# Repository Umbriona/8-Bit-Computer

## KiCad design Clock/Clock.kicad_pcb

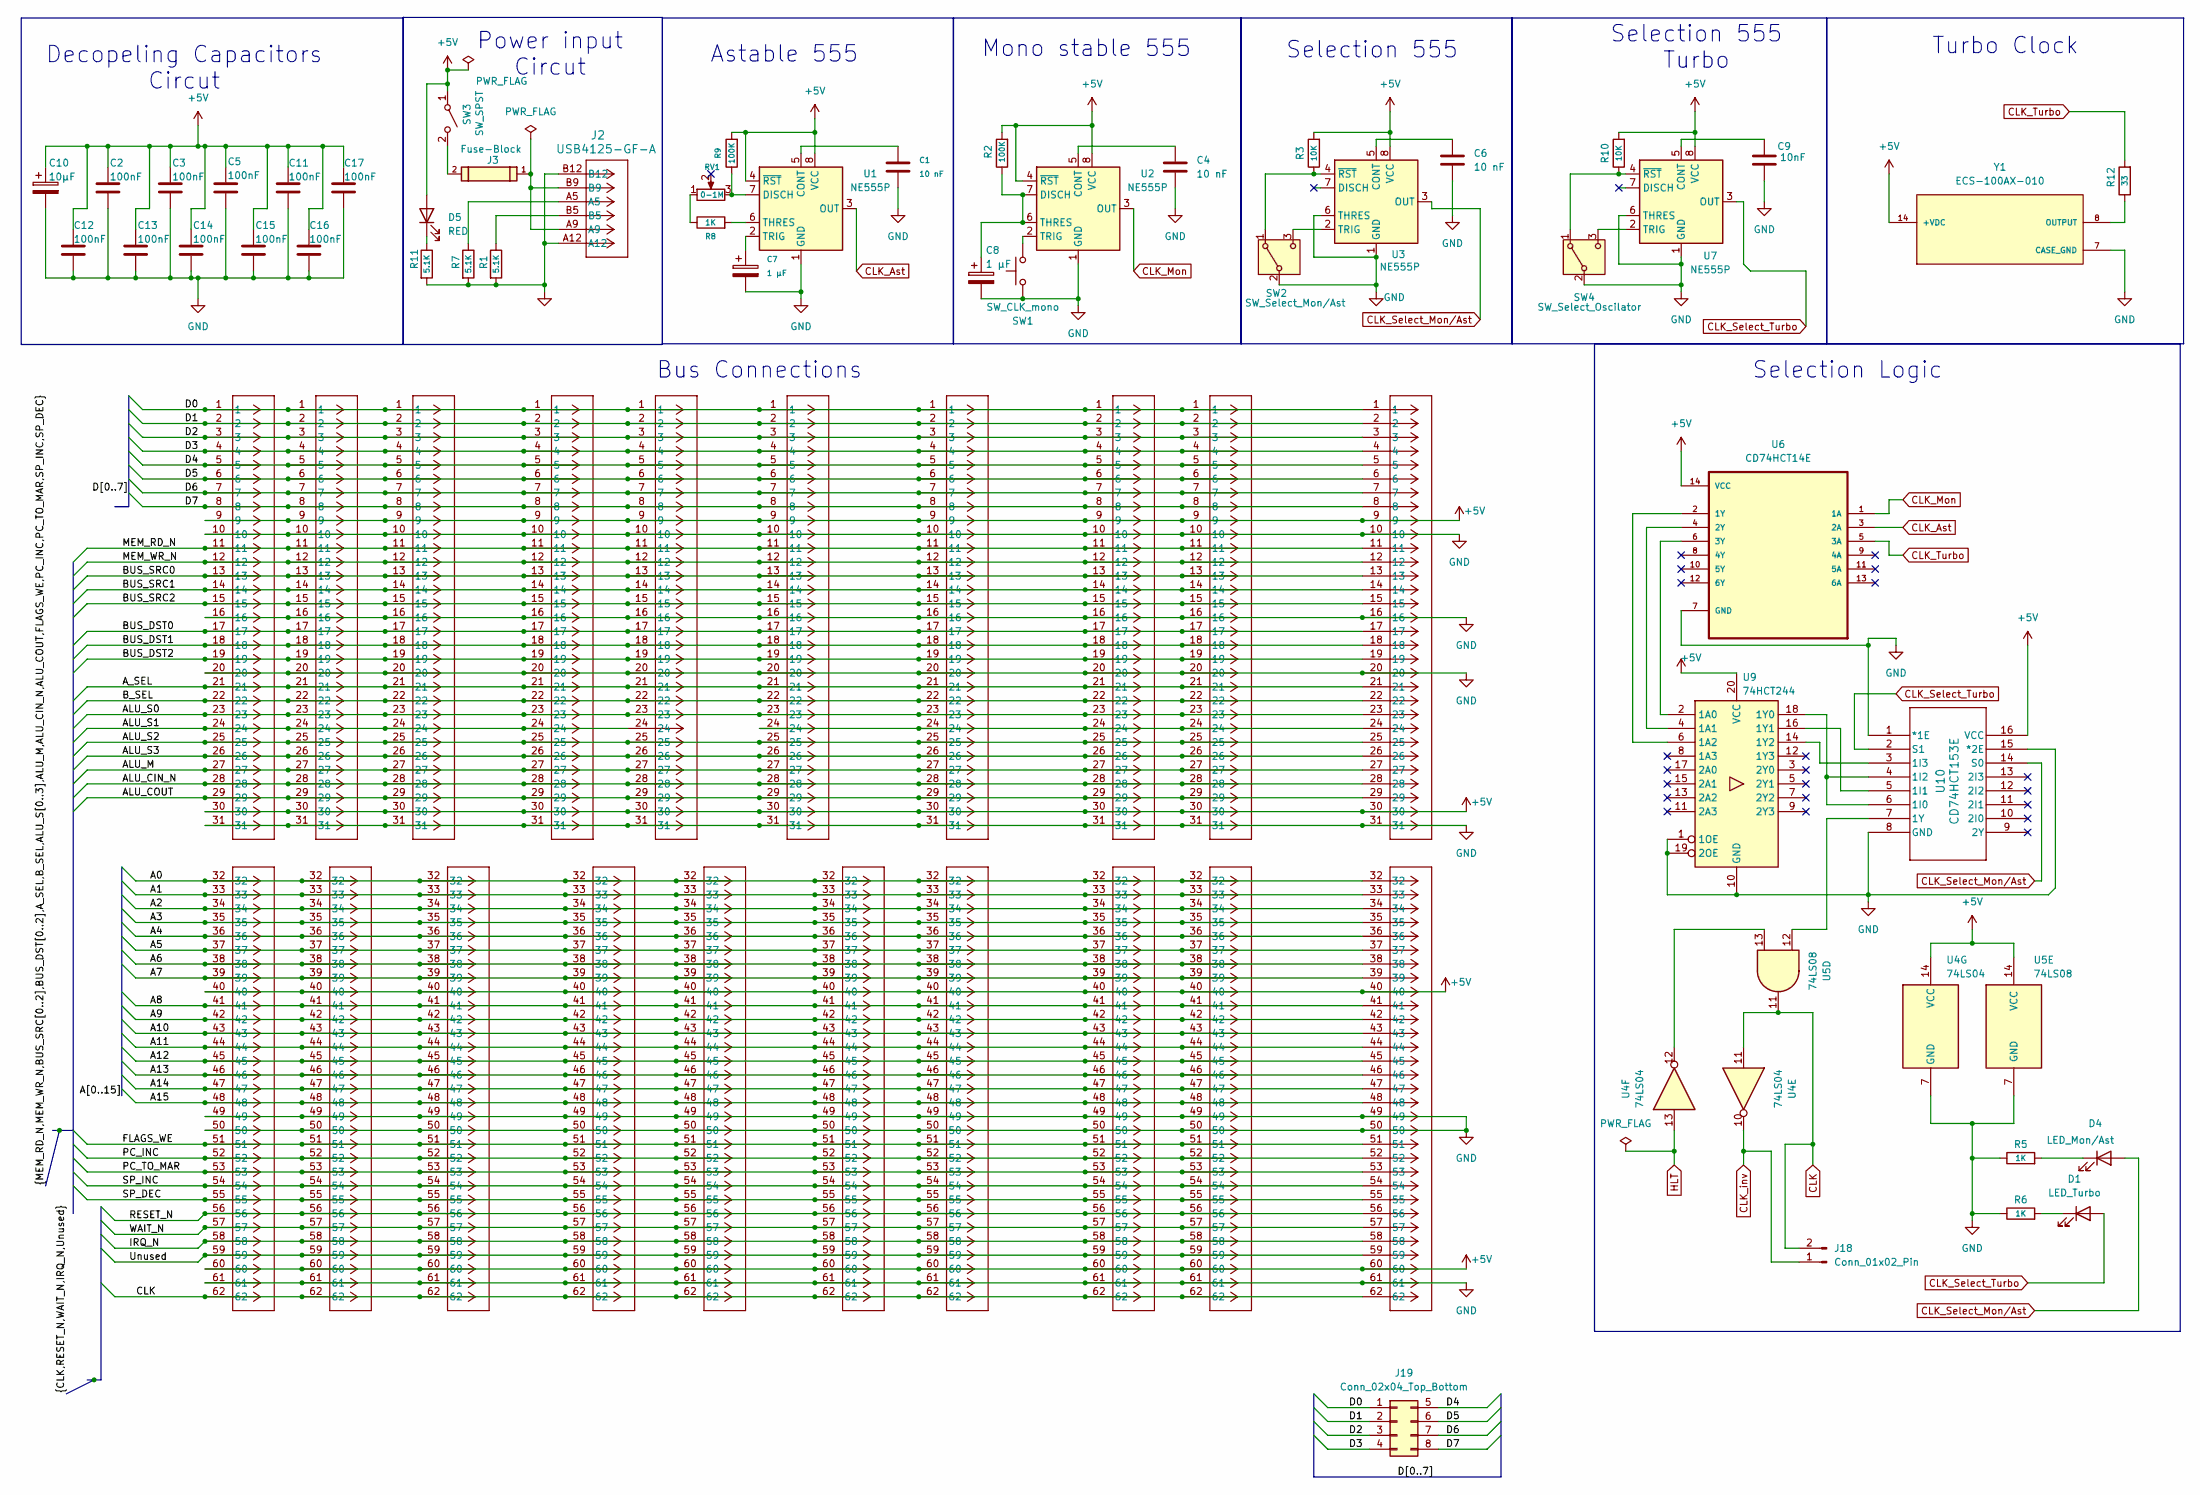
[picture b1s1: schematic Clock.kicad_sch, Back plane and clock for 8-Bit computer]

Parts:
C1, C4, C6: 10 nF; C_Disc_D3.0mm_W2.0mm_P2.50mm
C2, C3, C5, C11, C12, C13, C14, C15, C16, C17: 100nF; C_Disc_D3.0mm_W2.0mm_P2.50mm
C7, C8: 1 μF; CP_Radial_D4.0mm_P2.00mm
C9: 10nF; C_Disc_D3.0mm_W2.0mm_P2.50mm
C10: 10μF; CP_Radial_D5.0mm_P2.00mm
D1: LED_Turbo; LED_D5.0mm
D4: LED_Mon/Ast; LED_D5.0mm
D5: RED; LED_D5.0mm
J1, J4: Conn buss; CONN_520-350_EDA
J2: USB4125-GF-A; CONN6_USB4125_GCT
J3: Fuse-Block; 696108003002
J5, J6, J7, J8, J9, J10, J11, J12: Conn_buss; CONN_520-350_EDA
J18: Conn_01x02_Pin; PinHeader_1x02_P2.54mm_Vertical
J19: Conn_02x04_Top_Bottom; PinHeader_2x04_P2.54mm_Vertical
R1, R7, R11: 5.1K; R_Axial_DIN0204_L3.6mm_D1.6mm_P5.08mm_Horizontal
R2, R9: 100K; R_Axial_DIN0204_L3.6mm_D1.6mm_P5.08mm_Horizontal
R3, R10: 10K; R_Axial_DIN0204_L3.6mm_D1.6mm_P5.08mm_Horizontal
R5, R6, R8: 1K; R_Axial_DIN0204_L3.6mm_D1.6mm_P5.08mm_Horizontal
R12: 33; R_Axial_DIN0204_L3.6mm_D1.6mm_P5.08mm_Horizontal
RV1: 0-1M; PinHeader_1x03_P2.54mm_Vertical
SW1: SW_CLK_mono; PinHeader_1x02_P2.54mm_Vertical
SW2: SW_Select_Mon/Ast; PinHeader_1x03_P2.54mm_Vertical
SW3: SW_SPST; PinHeader_1x02_P2.54mm_Vertical
SW4: SW_Select_Oscilator; PinHeader_1x03_P2.54mm_Vertical
U1, U2, U3, U7: NE555P; DIP-8_W7.62mm
U4: 74LS04; DIP-14_W7.62mm
U5: 74LS08; DIP-14_W7.62mm
U6: CD74HCT14E
U9: 74HCT244
U10: CD74HCT153E; 74HCT153
Y1: ECS-100AX-010; OSC_ECS-100AX-010

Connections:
+5V: C2.1, C3.1, C5.1, C10.1, C11.1, C12.1, C13.1, C14.1, C15.1, C16.1, C17.1, D5.2 (A), J1.9, J1.30, J1.40, J1.60, J4.9, J4.30, J4.40, J4.60, J5.9, J5.30, J5.40, J5.60, J6.9, J6.30, J6.40, J6.60, J7.9, J7.30, J7.40, J7.60, J8.9, J8.30, J8.40, J8.60, J9.9, J9.30, J9.40, J9.60, J10.9, J10.30, J10.40, J10.60, J11.9, J11.30, J11.40, J11.60, J12.9, J12.30, J12.40, J12.60, R2.2, R3.2, R9.2, R10.2, SW3.1 (A), U1.4 (~RST), U1.8 (VCC), U2.4 (~RST), U2.8 (VCC), U3.8 (VCC), U4.14 (VCC), U5.14 (VCC), U6.14 (VCC), U7.8 (VCC), U9.20 (VCC), U10.16 (VCC), Y1.14 (+VDC)
/A0: J1.32, J4.32, J5.32, J6.32, J7.32, J8.32, J9.32, J10.32, J11.32, J12.32
/A1: J1.33, J4.33, J5.33, J6.33, J7.33, J8.33, J9.33, J10.33, J11.33, J12.33
/A2: J1.34, J4.34, J5.34, J6.34, J7.34, J8.34, J9.34, J10.34, J11.34, J12.34
/A3: J1.35, J4.35, J5.35, J6.35, J7.35, J8.35, J9.35, J10.35, J11.35, J12.35
/A4: J1.36, J4.36, J5.36, J6.36, J7.36, J8.36, J9.36, J10.36, J11.36, J12.36
/A5: J1.37, J4.37, J5.37, J6.37, J7.37, J8.37, J9.37, J10.37, J11.37, J12.37
/A6: J1.38, J4.38, J5.38, J6.38, J7.38, J8.38, J9.38, J10.38, J11.38, J12.38
/A7: J1.39, J4.39, J5.39, J6.39, J7.39, J8.39, J9.39, J10.39, J11.39, J12.39
/A8: J1.41, J4.41, J5.41, J6.41, J7.41, J8.41, J9.41, J10.41, J11.41, J12.41
/A9: J1.42, J4.42, J5.42, J6.42, J7.42, J8.42, J9.42, J10.42, J11.42, J12.42
/A10: J1.43, J4.43, J5.43, J6.43, J7.43, J8.43, J9.43, J10.43, J11.43, J12.43
/A11: J1.44, J4.44, J5.44, J6.44, J7.44, J8.44, J9.44, J10.44, J11.44, J12.44
/A12: J1.45, J4.45, J5.45, J6.45, J7.45, J8.45, J9.45, J10.45, J11.45, J12.45
/A13: J1.46, J4.46, J5.46, J6.46, J7.46, J8.46, J9.46, J10.46, J11.46, J12.46
/A14: J1.47, J4.47, J5.47, J6.47, J7.47, J8.47, J9.47, J10.47, J11.47, J12.47
/A15: J1.48, J4.48, J5.48, J6.48, J7.48, J8.48, J9.48, J10.48, J11.48, J12.48
/ALU_CIN_N: J1.28, J4.28, J5.28, J6.28, J7.28, J8.28, J9.28, J10.28, J11.28, J12.28
/ALU_COUT: J1.29, J4.29, J5.29, J6.29, J7.29, J8.29, J9.29, J10.29, J11.29, J12.29
/ALU_M: J1.27, J4.27, J5.27, J6.27, J7.27, J8.27, J9.27, J10.27, J11.27, J12.27
/ALU_S0: J1.23, J4.23, J5.23, J6.23, J7.23, J8.23, J9.23, J10.23, J11.23, J12.23
/ALU_S2: J1.25, J4.25, J5.25, J6.25, J7.25, J8.25, J9.25, J10.25, J11.25, J12.25
/ALU_S3: J1.26, J4.26, J5.26, J6.26, J7.26, J8.26, J9.26, J10.26, J11.26, J12.26
/A_SEL: J1.21, J4.21, J5.21, J6.21, J7.21, J8.21, J9.21, J10.21, J11.21, J12.21
/BUS_DST0: J1.17, J4.17, J5.17, J6.17, J7.17, J8.17, J9.17, J10.17, J11.17, J12.17
/BUS_DST1: J1.18, J4.18, J5.18, J6.18, J7.18, J8.18, J9.18, J10.18, J11.18, J12.18
/BUS_DST2: J1.19, J4.19, J5.19, J6.19, J7.19, J8.19, J9.19, J10.19, J11.19, J12.19
/BUS_SRC0: J1.13, J4.13, J5.13, J6.13, J7.13, J8.13, J9.13, J10.13, J11.13, J12.13
/BUS_SRC1: J1.14, J4.14, J5.14, J6.14, J7.14, J8.14, J9.14, J10.14, J11.14, J12.14
/BUS_SRC2: J1.15, J4.15, J5.15, J6.15, J7.15, J8.15, J9.15, J10.15, J11.15, J12.15
/B_SEL: J1.22, J4.22, J5.22, J6.22, J7.22, J8.22, J9.22, J10.22, J11.22, J12.22
/D0: J1.1, J4.1, J5.1, J6.1, J7.1, J8.1, J9.1, J10.1, J11.1, J12.1, J19.1
/D1: J1.2, J4.2, J5.2, J6.2, J7.2, J8.2, J9.2, J10.2, J11.2, J12.2, J19.2
/D2: J1.3, J4.3, J5.3, J6.3, J7.3, J8.3, J9.3, J10.3, J11.3, J12.3, J19.3
/D3: J1.4, J4.4, J5.4, J6.4, J7.4, J8.4, J9.4, J10.4, J11.4, J12.4, J19.4
/D4: J1.5, J4.5, J5.5, J6.5, J7.5, J8.5, J9.5, J10.5, J11.5, J12.5, J19.5
/D5: J1.6, J4.6, J5.6, J6.6, J7.6, J8.6, J9.6, J10.6, J11.6, J12.6, J19.6
/D6: J1.7, J4.7, J5.7, J6.7, J7.7, J8.7, J9.7, J10.7, J11.7, J12.7, J19.7
/D7: J1.8, J4.8, J5.8, J6.8, J7.8, J8.8, J9.8, J10.8, J11.8, J12.8, J19.8
/FLAGS_WE: J1.51, J4.51, J5.51, J6.51, J7.51, J8.51, J9.51, J10.51, J11.51, J12.51
/IRQ_N: J1.58, J4.58, J5.58, J6.58, J7.58, J8.58, J9.58, J10.58, J11.58, J12.58
/MEM_RD_N: J1.11, J4.11, J5.11, J6.11, J7.11, J8.11, J9.11, J10.11, J11.11, J12.11
/MEM_WR_N: J1.12, J4.12, J5.12, J6.12, J7.12, J8.12, J9.12, J10.12, J11.12, J12.12
/PC_INC: J1.52, J4.52, J5.52, J6.52, J7.52, J8.52, J9.52, J10.52, J11.52, J12.52
/PC_TO_MAR: J1.53, J4.53, J5.53, J6.53, J7.53, J8.53, J9.53, J10.53, J11.53, J12.53
/RESET_N: J1.56, J4.56, J5.56, J6.56, J7.56, J8.56, J9.56, J10.56, J11.56, J12.56
/SP_DEC: J1.55, J4.55, J5.55, J6.55, J7.55, J8.55, J9.55, J10.55, J11.55, J12.55
/SP_INC: J1.54, J4.54, J5.54, J6.54, J7.54, J8.54, J9.54, J10.54, J11.54, J12.54
/Unused: J1.59, J4.59, J5.59, J6.59, J7.59, J8.59, J9.59, J10.59, J11.59, J12.59
/WAIT_N: J1.57, J4.57, J5.57, J6.57, J7.57, J8.57, J9.57, J10.57, J11.57, J12.57
CLK: J1.62, J4.62, J5.62, J6.62, J7.62, J8.62, J9.62, J10.62, J11.62, J12.62, J18.2, U4.11, U5.11
CLK_Ast: U1.3 (OUT), U6.3 (2A)
CLK_Mon: U2.3 (OUT), U6.1 (1A)
CLK_Select_Mon/Ast: D4.2 (A), U3.3 (OUT), U10.14 (S0)
CLK_Select_Turbo: D1.2 (A), U7.3 (OUT), U10.2 (S1)
CLK_Turbo: R12.2, U6.5 (3A)
CLK_inv: J18.1, U4.10
GND: C1.2, C2.2, C3.2, C4.2, C5.2, C6.2, C7.2, C8.2, C9.2, C10.2, C11.2, C12.2, C13.2, C14.2, C15.2, C16.2, C17.2, J1.10, J1.16, J1.20, J1.31, J1.49, J1.50, J1.61, J2.A12, J2.B12, J4.10, J4.16, J4.20, J4.31, J4.49, J4.50, J4.61, J5.10, J5.16, J5.20, J5.31, J5.49, J5.50, J5.61, J6.10, J6.16, J6.20, J6.31, J6.49, J6.50, J6.61, J7.10, J7.16, J7.20, J7.31, J7.49, J7.50, J7.61, J8.10, J8.16, J8.20, J8.31, J8.49, J8.50, J8.61, J9.10, J9.16, J9.20, J9.31, J9.49, J9.50, J9.61, J10.10, J10.16, J10.20, J10.31, J10.49, J10.50, J10.61, J11.10, J11.16, J11.20, J11.31, J11.49, J11.50, J11.61, J12.10, J12.16, J12.20, J12.31, J12.49, J12.50, J12.61, R1.2, R5.1, R6.1, R7.2, R11.2, SW1.1, SW2.2 (B), SW4.2 (B), U1.1 (GND), U2.1 (GND), U3.1 (GND), U3.6 (THRES), U4.7 (GND), U5.7 (GND), U6.7 (GND), U7.1 (GND), U7.6 (THRES), U9.1 (1OE), U9.10 (GND), U9.19 (2OE), U10.1 (*1E), U10.8 (GND), U10.15 (*2E), Y1.7 (CASE_GND)
HLT: U4.13
unnamed: D1.1 (K), R6.2
unnamed: D4.1 (K), R5.2
unnamed: D5.1 (K), R11.1
unnamed: J2.A5, R7.1
unnamed: J2.A9, J2.B9, J3.1
unnamed: J2.B5, R1.1
unnamed: R8.1, RV1.1
unnamed: R3.1, SW2.1 (A), U3.4 (~RST)
unnamed: SW2.3 (C), U3.2 (TRIG)
unnamed: J3.2, SW3.2 (B)
unnamed: R10.1, SW4.1 (A), U7.4 (~RST)
unnamed: SW4.3 (C), U7.2 (TRIG)
unnamed: C1.1, U1.5 (CONT)
unnamed: R9.1, RV1.3, U1.7 (DISCH)
unnamed: R8.2, U1.6 (THRES)
unnamed: C7.1, U1.2 (TRIG)
unnamed: C4.1, U2.5 (CONT)
unnamed: C8.1, R2.1, U2.6 (THRES), U2.7 (DISCH)
unnamed: SW1.2, U2.2 (TRIG)
unnamed: C6.1, U3.5 (CONT)
unnamed: U4.12, U5.13
unnamed: U6.2 (1Y), U9.6 (1A2)
unnamed: U6.4 (2Y), U9.4 (1A1)
unnamed: U6.6 (3Y), U9.2 (1A0)
unnamed: C9.1, U7.5 (CONT)
unnamed: U9.18 (1Y0), U10.4 (1I2), U10.6 (1I0)
unnamed: U9.16 (1Y1), U10.5 (1I1)
unnamed: U9.14 (1Y2), U10.3 (1I3)
unnamed: U5.12, U10.7 (1Y)
unnamed: R12.1, Y1.8 (OUTPUT)

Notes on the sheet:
Selection 555
Astable 555
Mono stable 555
Power input Circut
Turbo Clock
Bus Connections
Selection 555 Turbo
Selection Logic
Decopeling Capacitors Circut

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
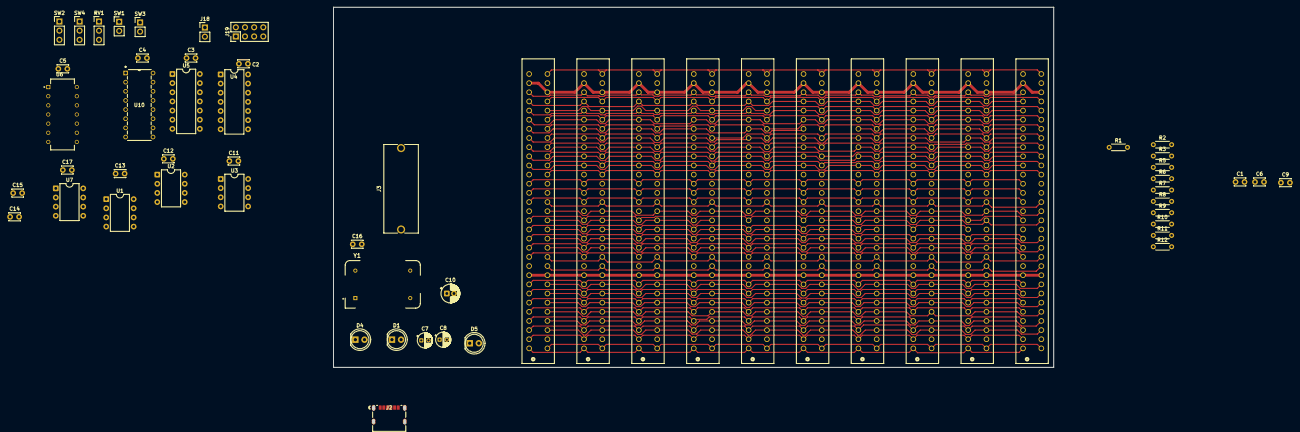
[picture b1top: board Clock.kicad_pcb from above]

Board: 2 copper layers, 200.0 x 115.4 mm, 59 parts (0 on the bottom side), 84 nets.

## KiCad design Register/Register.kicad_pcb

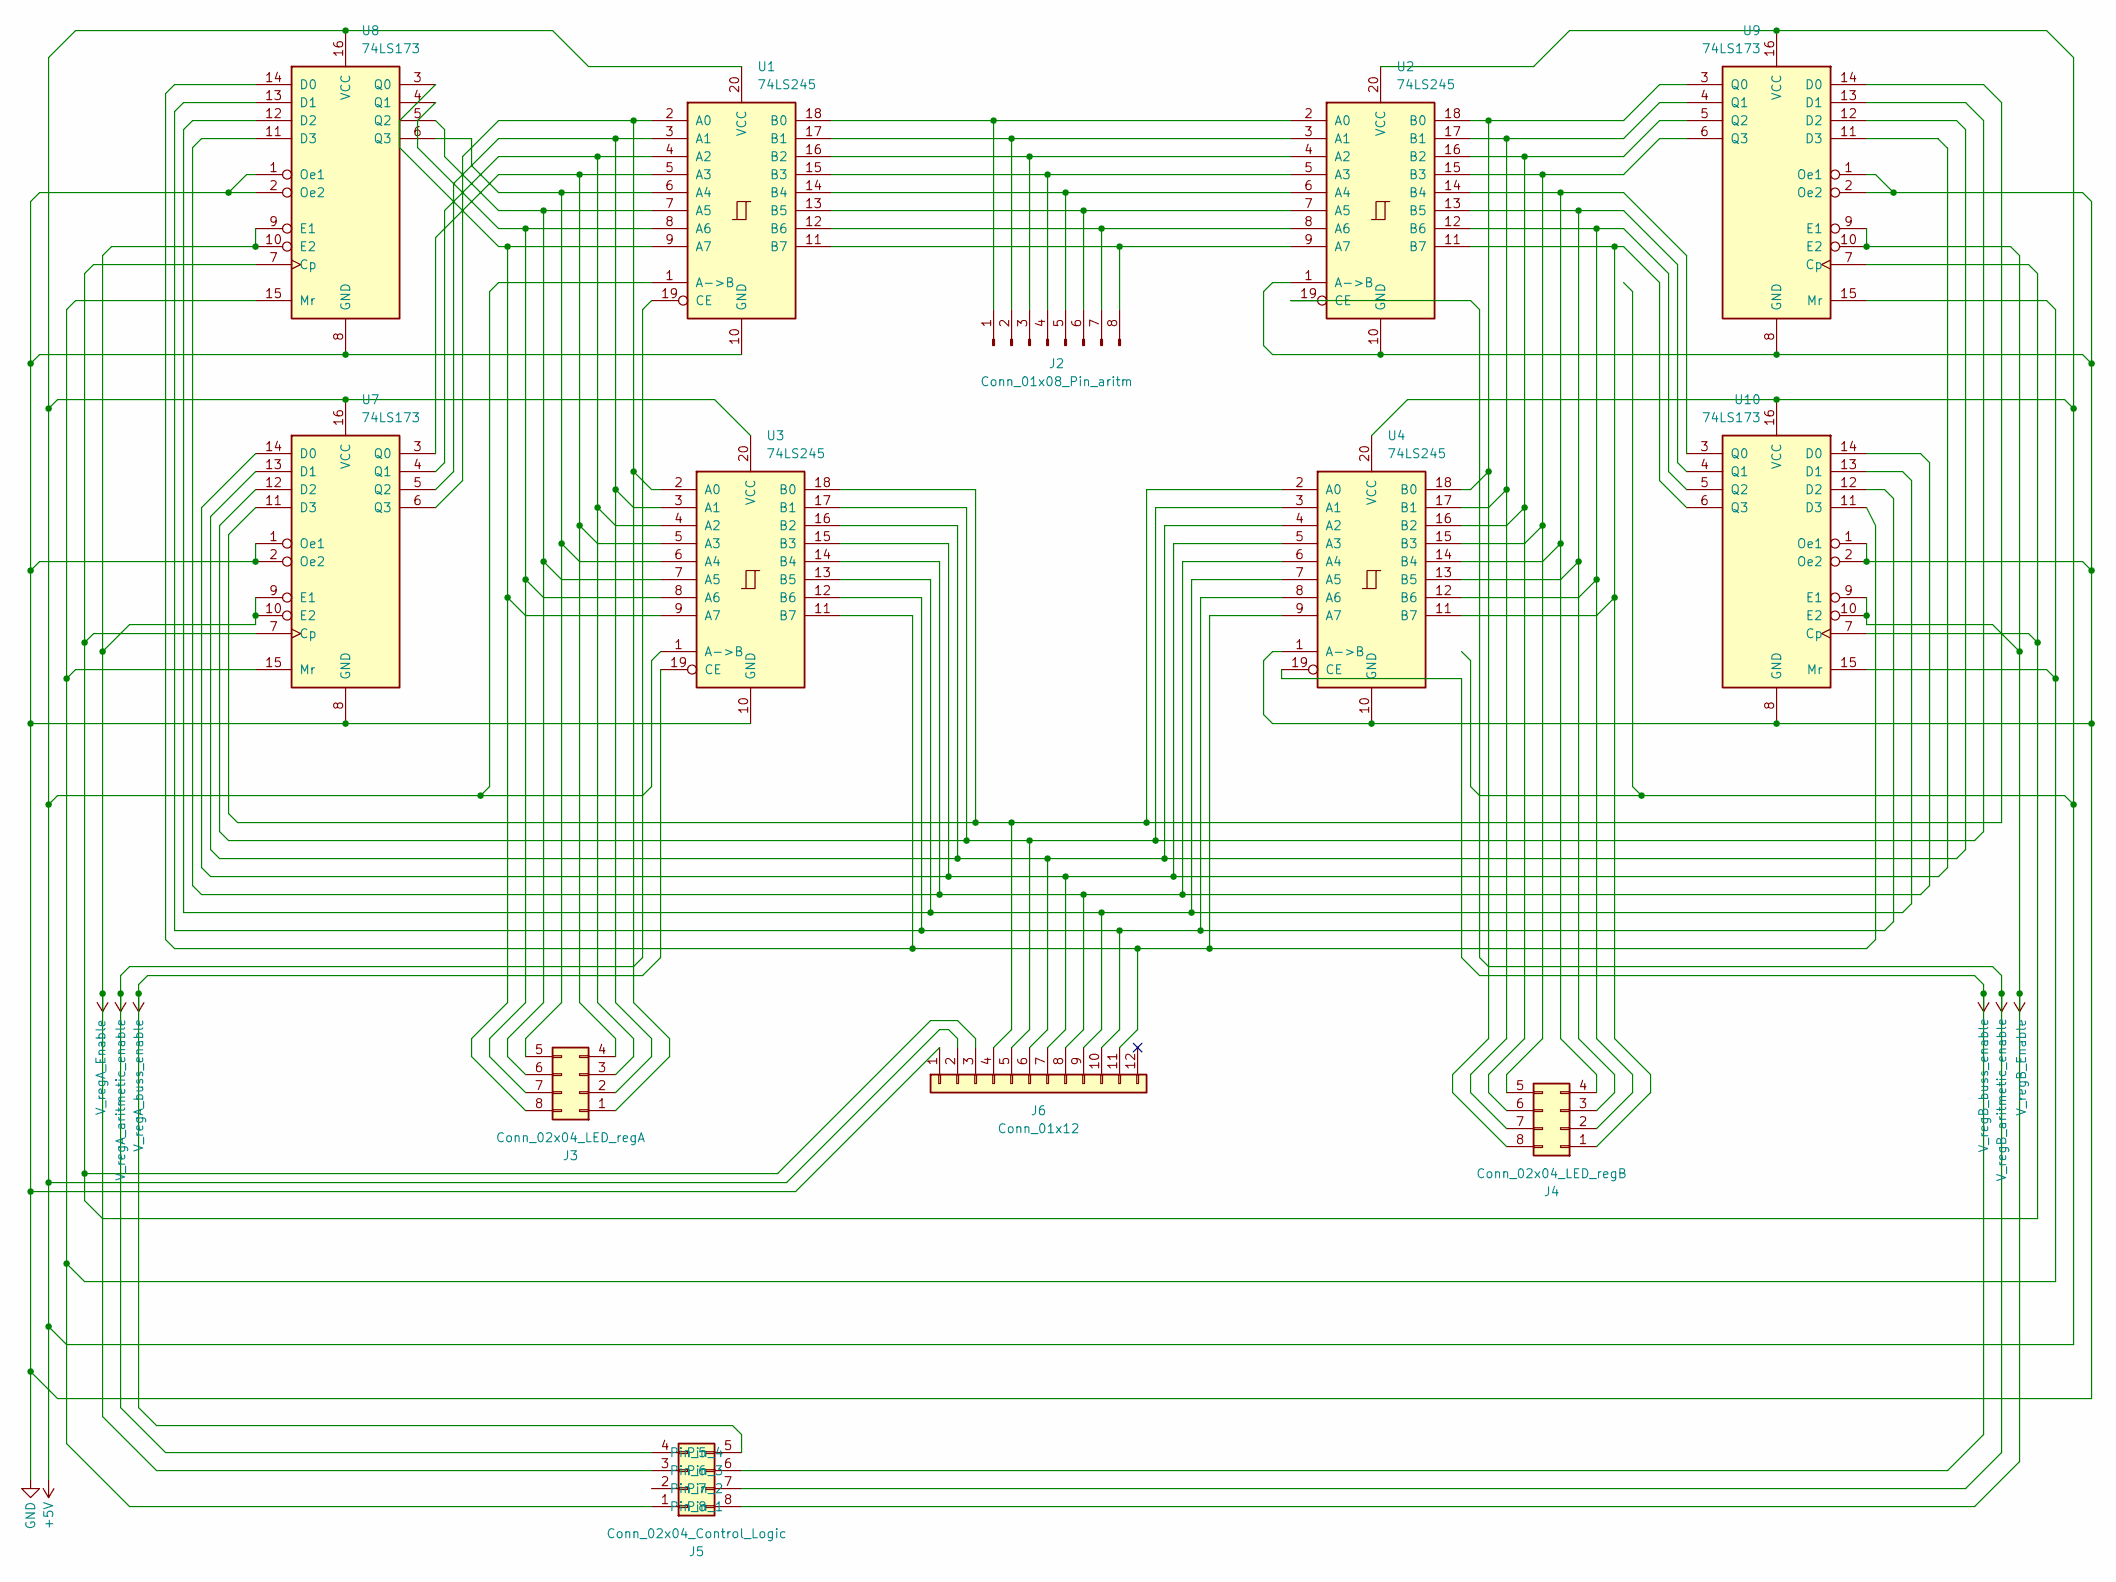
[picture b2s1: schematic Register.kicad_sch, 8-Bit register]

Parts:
J2: Conn_01x08_Pin_aritm; PinHeader_1x08_P2.54mm_Horizontal
J3: Conn_02x04_LED_regA; PinSocket_2x04_P2.54mm_Horizontal
J4: Conn_02x04_LED_regB; PinSocket_2x04_P2.54mm_Horizontal
J5: Conn_02x04_Control_Logic; PinSocket_2x04_P2.54mm_Horizontal
J6: Conn_01x12; PinHeader_1x12_P2.54mm_Horizontal
U1, U2, U3, U4: 74LS245; DIP-20_W7.62mm
U7, U8, U9, U10: 74LS173; DIP-16_W10.16mm

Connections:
+5V: J6.2, U1.1 (A->B), U1.20 (VCC), U2.20 (VCC), U3.1 (A->B), U3.20 (VCC), U4.20 (VCC), U7.16 (VCC), U8.16 (VCC), U9.16 (VCC), U10.16 (VCC)
GND: J6.1, U1.10 (GND), U2.1 (A->B), U2.10 (GND), U3.10 (GND), U4.1 (A->B), U4.10 (GND), U7.1 (Oe1), U7.2 (Oe2), U7.8 (GND), U8.1 (Oe1), U8.2 (Oe2), U8.8 (GND), U9.1 (Oe1), U9.2 (Oe2), U9.8 (GND), U10.1 (Oe1), U10.2 (Oe2), U10.8 (GND)
unnamed: J2.1, U1.18 (B0), U2.2 (A0)
unnamed: J2.2, U1.17 (B1), U2.3 (A1)
unnamed: J2.3, U1.16 (B2), U2.4 (A2)
unnamed: J2.4, U1.15 (B3), U2.5 (A3)
unnamed: J2.5, U1.14 (B4), U2.6 (A4)
unnamed: J2.6, U1.13 (B5), U2.7 (A5)
unnamed: J2.7, U1.12 (B6), U2.8 (A6)
unnamed: J2.8, U1.11 (B7), U2.9 (A7)
unnamed: J3.1, U1.2 (A0), U3.2 (A0), U7.6 (Q3)
unnamed: J3.2, U1.3 (A1), U3.3 (A1), U7.5 (Q2)
unnamed: J3.3, U1.4 (A2), U3.4 (A2), U7.4 (Q1)
unnamed: J3.4, U1.5 (A3), U3.5 (A3), U7.3 (Q0)
unnamed: J3.5, U1.6 (A4), U3.6 (A4), U8.6 (Q3)
unnamed: J3.6, U1.7 (A5), U3.7 (A5), U8.5 (Q2)
unnamed: J3.7, U1.8 (A6), U3.8 (A6), U8.4 (Q1)
unnamed: J3.8, U1.9 (A7), U3.9 (A7), U8.3 (Q0)
unnamed: J4.1, U2.11 (B7), U4.11 (B7), U10.6 (Q3)
unnamed: J4.2, U2.12 (B6), U4.12 (B6), U10.5 (Q2)
unnamed: J4.3, U2.13 (B5), U4.13 (B5), U10.4 (Q1)
unnamed: J4.4, U2.14 (B4), U4.14 (B4), U10.3 (Q0)
unnamed: J4.5, U2.15 (B3), U4.15 (B3), U9.6 (Q3)
unnamed: J4.6, U2.16 (B2), U4.16 (B2), U9.5 (Q2)
unnamed: J4.7, U2.17 (B1), U4.17 (B1), U9.4 (Q1)
unnamed: J4.8, U2.18 (B0), U4.18 (B0), U9.3 (Q0)
unnamed: J5.1, U7.15 (Mr), U8.15 (Mr), U9.15 (Mr), U10.15 (Mr)
unnamed: J6.3, U7.7 (Cp), U8.7 (Cp), U9.7 (Cp), U10.7 (Cp)
unnamed: J6.4, U3.18 (B0), U4.2 (A0), U7.11 (D3), U9.14 (D0)
unnamed: J6.5, U3.17 (B1), U4.3 (A1), U7.12 (D2), U9.13 (D1)
unnamed: J6.6, U3.16 (B2), U4.4 (A2), U7.13 (D1), U9.12 (D2)
unnamed: J6.7, U3.15 (B3), U4.5 (A3), U7.14 (D0), U9.11 (D3)
unnamed: J6.8, U3.14 (B4), U4.6 (A4), U8.11 (D3), U10.14 (D0)
unnamed: J6.9, U3.13 (B5), U4.7 (A5), U8.12 (D2), U10.13 (D1)
unnamed: J6.10, U3.12 (B6), U4.8 (A6), U8.13 (D1), U10.12 (D2)
unnamed: J6.11, U3.11 (B7), U4.9 (A7), U8.14 (D0), U10.11 (D3)
V_regA_Enable: J5.3, U7.9 (E1), U7.10 (E2), U8.9 (E1), U8.10 (E2)
V_regA_aritmetic_enable: J5.4, U1.19 (CE)
V_regA_buss_enable: J5.5, U3.19 (CE)
V_regB_Enable: J5.8, U9.9 (E1), U9.10 (E2), U10.9 (E1), U10.10 (E2)
V_regB_aritmetic_enable: J5.7, U2.19 (CE)
V_regB_buss_enable: J5.6, U4.19 (CE)

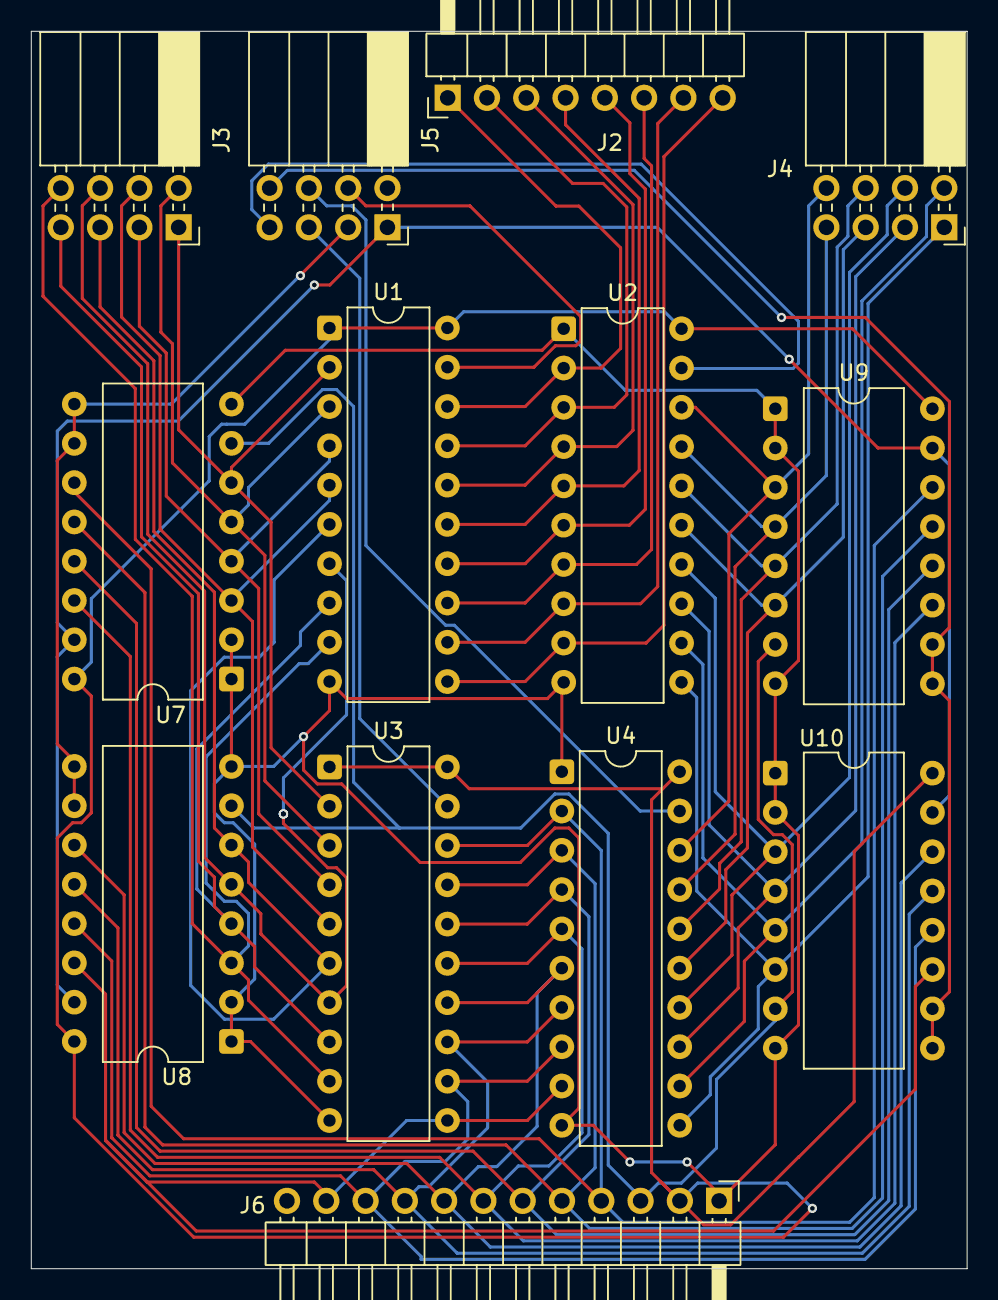
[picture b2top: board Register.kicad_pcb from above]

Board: 2 copper layers, 60.5 x 80.0 mm, 13 parts (0 on the bottom side), 42 nets.

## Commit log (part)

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2026-05-15 First iteration of Clock and backplane
2026-05-17 Changed backplane signal layout, connected data bus
2026-05-18 Routed bus connector
